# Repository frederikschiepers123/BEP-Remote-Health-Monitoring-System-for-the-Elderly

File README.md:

# Remote Health Monitoring System for the Elderly

TU Delft BSc Applied Project (BAP). A three-tier system that passively monitors
an elderly person at home — mmWave radar vitals (heart/breath rate, presence),
environment, air quality, light — and delivers the data to a hospital-side
FHIR R4 endpoint, with a smart-mirror UI in the home:

```
┌──────────────────┐   MQTT/mTLS   ┌──────────────────────┐   MQTT/mTLS   ┌──────────────┐   FHIR R4   ┌──────────┐
│  Sensor module   │ ────────────► │  Android tablet      │ ◄──────────── │  SBC         │ ──────────► │ Hospital │
│  Pico 2 W (C11)  │               │  Mosquitto broker    │               │  aggregator  │             │ endpoint │
│  radar/env/air/  │               │  + MagicMirror² UI   │               │  (Python,    │             │ (HAPI in │
│  light + OLED    │               │  behind the mirror   │               │  sbc/)       │             │  dev)    │
└──────────────────┘               └──────────────────────┘               └──────────────┘             └──────────┘
```

Every byte between tiers is mTLS-encrypted (ECDSA P-256, project CA, static
factory-provisioned certs). The firmware publishes raw JSON samples on
`rmms/<uuid>/...`; the mirror and the SBC are independent subscribers of the
same topics.

## Read this first (in order)

1. **[`CLAUDE.md`](CLAUDE.md)** — the firmware + system architecture contract.
   Single source of truth; everything else defers to it.
2. **[`docs/CLAUDE_tablet.md`](docs/CLAUDE_tablet.md)** — the tablet tier
   (broker, MagicMirror², mDNS, presence→screen coupling, autostart).
3. **[`sbc/CLAUDE.md`](sbc/CLAUDE.md)** — the SBC aggregator / FHIR tier.
4. **[`docs/handover.md`](docs/handover.md)** — what is hardware-proven vs
   built-only, known hardware/network gotchas, and CA/cert custody.

## Repository map

| Path | What it is |
|---|---|
| `CLAUDE.md`, `DEMO.md` | The architecture contract and the end-to-end demo runbook (see reading order above / quickstarts below). |
| `main/`, `components/` | **Pico 2 W firmware** (C11; pico-sdk + FreeRTOS + lwIP/mbedTLS + littlefs). One component per concern — layout in `CLAUDE.md §6`. |
| `test/host/` | Native unit tests (CMocka) for driver logic — `bash test/host/run.sh`. |
| `test/bringup/` | Standalone bring-up/diagnostic firmware images (blink → sensors → Wi-Fi → mTLS → full bench). `bringup_sensors` is the demo image. |
| `docs/` | System docs: bring-up procedure, MQTT topic contract, pin map, ADRs, provisioning, handover, technical audit of the previous group's code. |
| `scripts/` | Operational scripts: build, CA + device provisioning, tablet deploy/boot, demo startup, broker ACL test. Index: `scripts/README.md`. |
| `sbc/` | **SBC aggregator** — standalone Python project (own README, RUNBOOK, CLAUDE.md, tests). Never compiled into the firmware. |
| `MagicMirror/` | Vendored upstream MagicMirror² tree (see its README). Project work lives only in `modules/MMM-SensorUI/`, `modules/MMM-CustomMQTTBridge/`, `css/`, `config/` — the live `config.js` holds LAN specifics, is gitignored, and lives on the tablet; `config/config.custom.sample.js` is a UI-only starter. |
| `HealthMonitorWakeTest/` | **Android wake app** (Android Studio project): radar presence ↔ tablet screen on/off via the localhost MQTT listener (ADR-0004). See its README. |
| `apk/` | Prebuilt APK of the wake app. |
| `fully/` | Exported settings for the optional Fully Kiosk Browser (mirror kiosk mode). |
| `third_party/` | Git submodules: FreeRTOS-Kernel, littlefs. **pico-sdk is not vendored** — see the firmware quickstart. |
| `documents_and_diagrams/` | Thesis report, defense presentation, system diagrams. |
| `papers/` | Reference papers + the complete reference list. |
| `lasercutting_files/` | Enclosure/acrylic lasercutting files (DXF + Fusion 360). |
| `PCB/` | This group's KiCad PCB design files + bench measurements (buck converter scope shots). |
| `Readout Code HMMD-MR60BHA2 and BMP/` | Standalone sensor-readout experiments (radar filtering tests, BMP readout) used during bring-up — not part of the production firmware. |

**Local / generated directories (never in git):** `build*/` are CMake output
trees; `out/` is provisioning output created by `scripts/provision_ca.sh` —
it holds device/broker/mirror certificate bundles **including private keys**
and must never be committed (it is gitignored; see `docs/provisioning.md`).
On a fresh clone neither exists until you build/provision.

The **previous BAP group's material** (`bestanden_vorige_BAP/`) was removed
from the tree during handover cleanup — it is reference-only and available in
git history (any pre-July-2026 commit). Their registration protocol was
audited (`docs/technical-audit.md`) and deliberately replaced
(`CLAUDE.md §9.4`); their committed private keys are burned — never reuse
anything cryptographic from that tree.

## Quickstart per tier

### Firmware (Pico 2 W)

```bash
git clone --recurse-submodules <this-repo>            # brings FreeRTOS-Kernel + littlefs
git clone https://github.com/raspberrypi/pico-sdk.git ~/pico/pico-sdk
(cd ~/pico/pico-sdk && git submodule update --init)
export PICO_SDK_PATH=~/pico/pico-sdk

mkdir build && cd build
cmake -DPICO_BOARD=pico2_w -DCMAKE_BUILD_TYPE=Debug ..
cmake --build . -j$(nproc)
# → main/sensor_module.uf2 (production) + test/bringup/*.uf2 (bring-up images)
```

Flash: hold BOOTSEL while plugging in, copy the `.uf2` to the mounted drive
(details + SWD alternative: `CLAUDE.md §5`). Bring-up order with expected
results per step: `docs/bring_up.md`. Host tests: `bash test/host/run.sh`.

### Certificates + device provisioning

Identity is factory-provisioned: certs are generated **off-device** by the
project CA and written to the Pico's littlefs; there is no enrollment protocol
(`CLAUDE.md §9.4`). The full procedure — CA creation, broker/mirror/operator/
device bundles, `bringup_provision.uf2` + `scripts/provision_device.py` — is in
**[`docs/provisioning.md`](docs/provisioning.md)**. The CA private key is *not*
in this repo; custody is covered in `docs/handover.md`.

### Tablet (broker + mirror)

`scripts/deploy_home_kit.sh` provisions/deploys the whole tablet kit over ssh
(Termux); `scripts/tablet_boot.sh` + Termux:Boot make the tablet self-healing
across reboots. Tier spec: `docs/CLAUDE_tablet.md`.

### SBC aggregator (FHIR)

```bash
cd sbc && python3 -m venv .venv && .venv/bin/pip install -e .[dev]
.venv/bin/python -m pytest tests -q
```

Full install/run/prove-the-FHIR-output walkthrough: `sbc/RUNBOOK.md`.

### End-to-end demo

Full session procedure: **[`DEMO.md`](DEMO.md)**. In short:
`scripts/demo_start.sh <tablet-ip>` starts a demo session; a provisioned Pico
running `bringup_sensors.uf2` publishes live sensor data and the mirror renders
it. Networking caveats (use a phone hotspot, not eduroam; keep the tablet
awake) are in `docs/handover.md`.

## Where the contracts live

- MQTT topics + JSON payload schema: `CLAUDE.md §9`, `docs/mqtt_topics.md`.
- Sensor-JSON → FHIR mapping: `CLAUDE.md §9.6` (firmware side) and
  `sbc/docs/fhir-mapping.md` (generated LOINC/UCUM table).
- Mirror UI boundary (raw topics, JS-side thresholds, two-namespace design):
  `CLAUDE.md §9.5`/`§9.5.1` and the module READMEs under `MagicMirror/modules/`.
- Cross-tier loss-tolerance + idempotency: `docs/sbc-failover-and-idempotency.md`.

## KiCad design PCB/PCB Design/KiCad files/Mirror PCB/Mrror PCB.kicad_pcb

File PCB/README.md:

# PCB/

- `PCB Design/` — all KiCad files.
- `Buck_images/` — oscilloscope photos from testing the buck-converter
  circuit on the PCB (directory names give the load condition).

## Which files are authoritative

- **Generic (sensor-module) board:**
  `PCB Design/KiCad files/Generic PCB/Generic PCB/Generic PCB.kicad_pcb`
  (+ matching `.kicad_sch`/`.kicad_pro`). Note the doubled `Generic PCB/`
  nesting is a KiCad project-folder artifact — descend twice.
- **Mirror board:**
  `PCB Design/KiCad files/Mirror PCB/Mrror PCB.kicad_pcb`
  (+ matching `.kicad_sch`/`.kicad_pro`).

Caveats for the next group:

- The `Mrror` spelling is a typo, but it is **load-bearing**: KiCad project
  files cross-reference each other by name — do not rename.
- Some `Mrror PCB*` artifacts (silkscreen PDFs, `Mrror_PCB_routed_v1.kicad_pcb`)
  also sit inside the *Generic* board's folder; the Mirror board's canonical
  files are the ones under `Mirror PCB/`.
- KiCad autosave/backup droppings (`_restore_backup_*`, `*.lck`, `*.bak`,
  `*_chatgpt*.zip`) were deleted at handover and are now gitignored.
- Known board erratum: the I²C bus lacks pull-ups — fit 4.7 kΩ from GP8/GP9
  to 3V3 (see `docs/handover.md`).

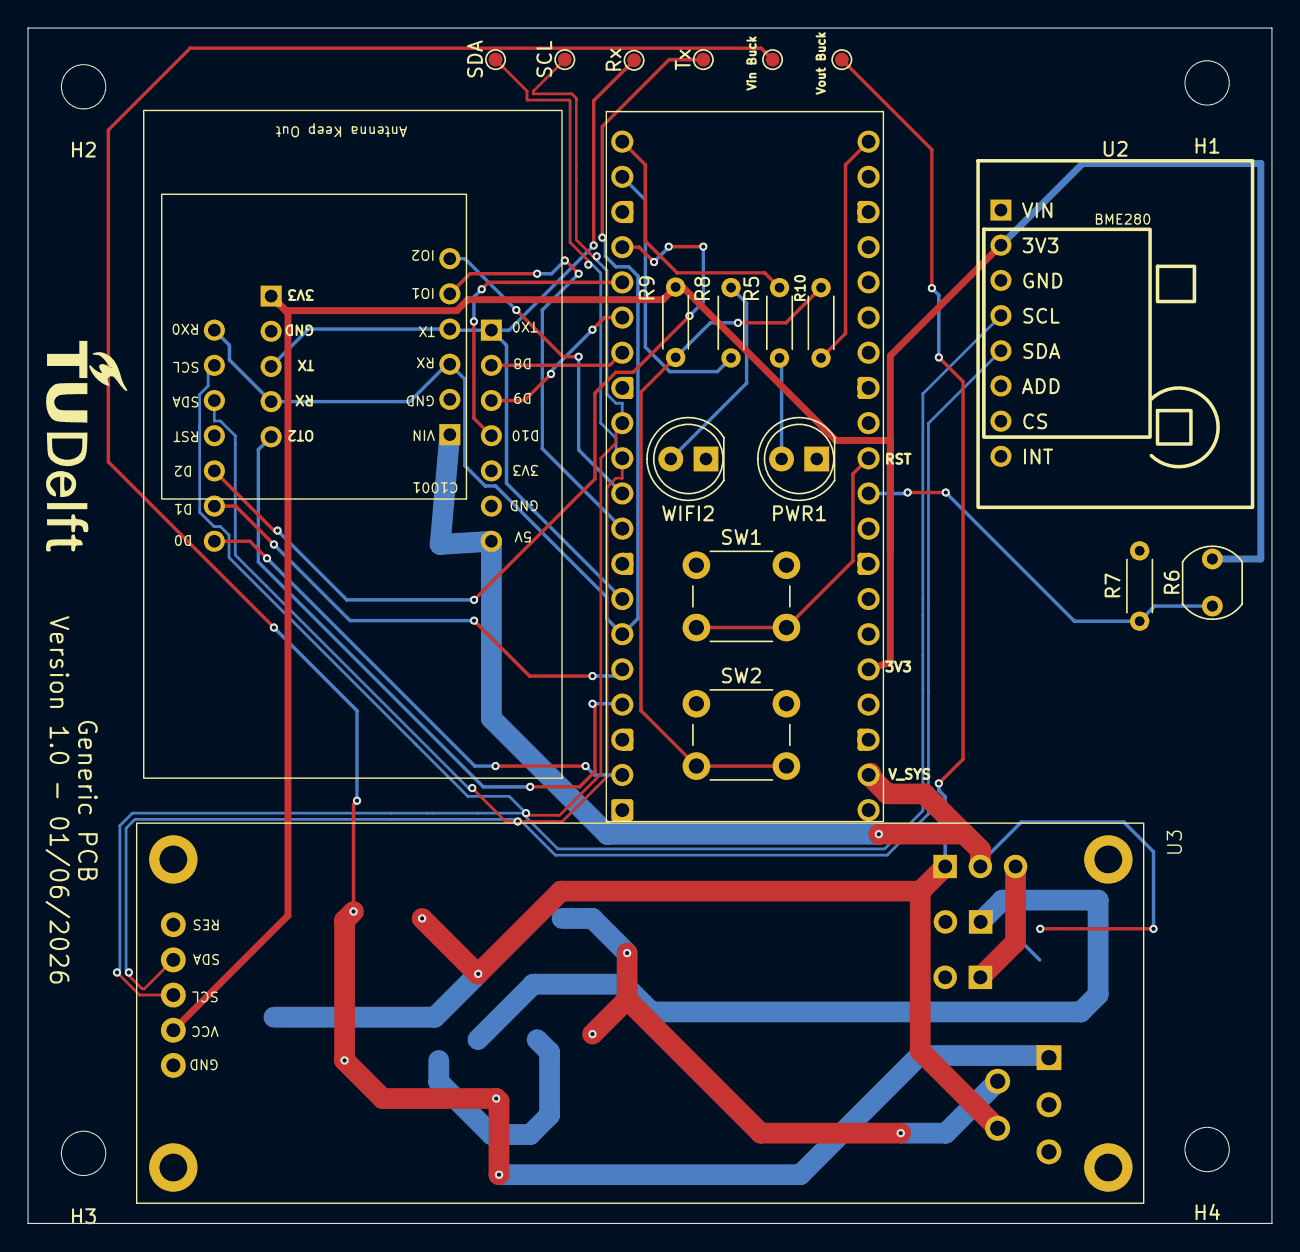
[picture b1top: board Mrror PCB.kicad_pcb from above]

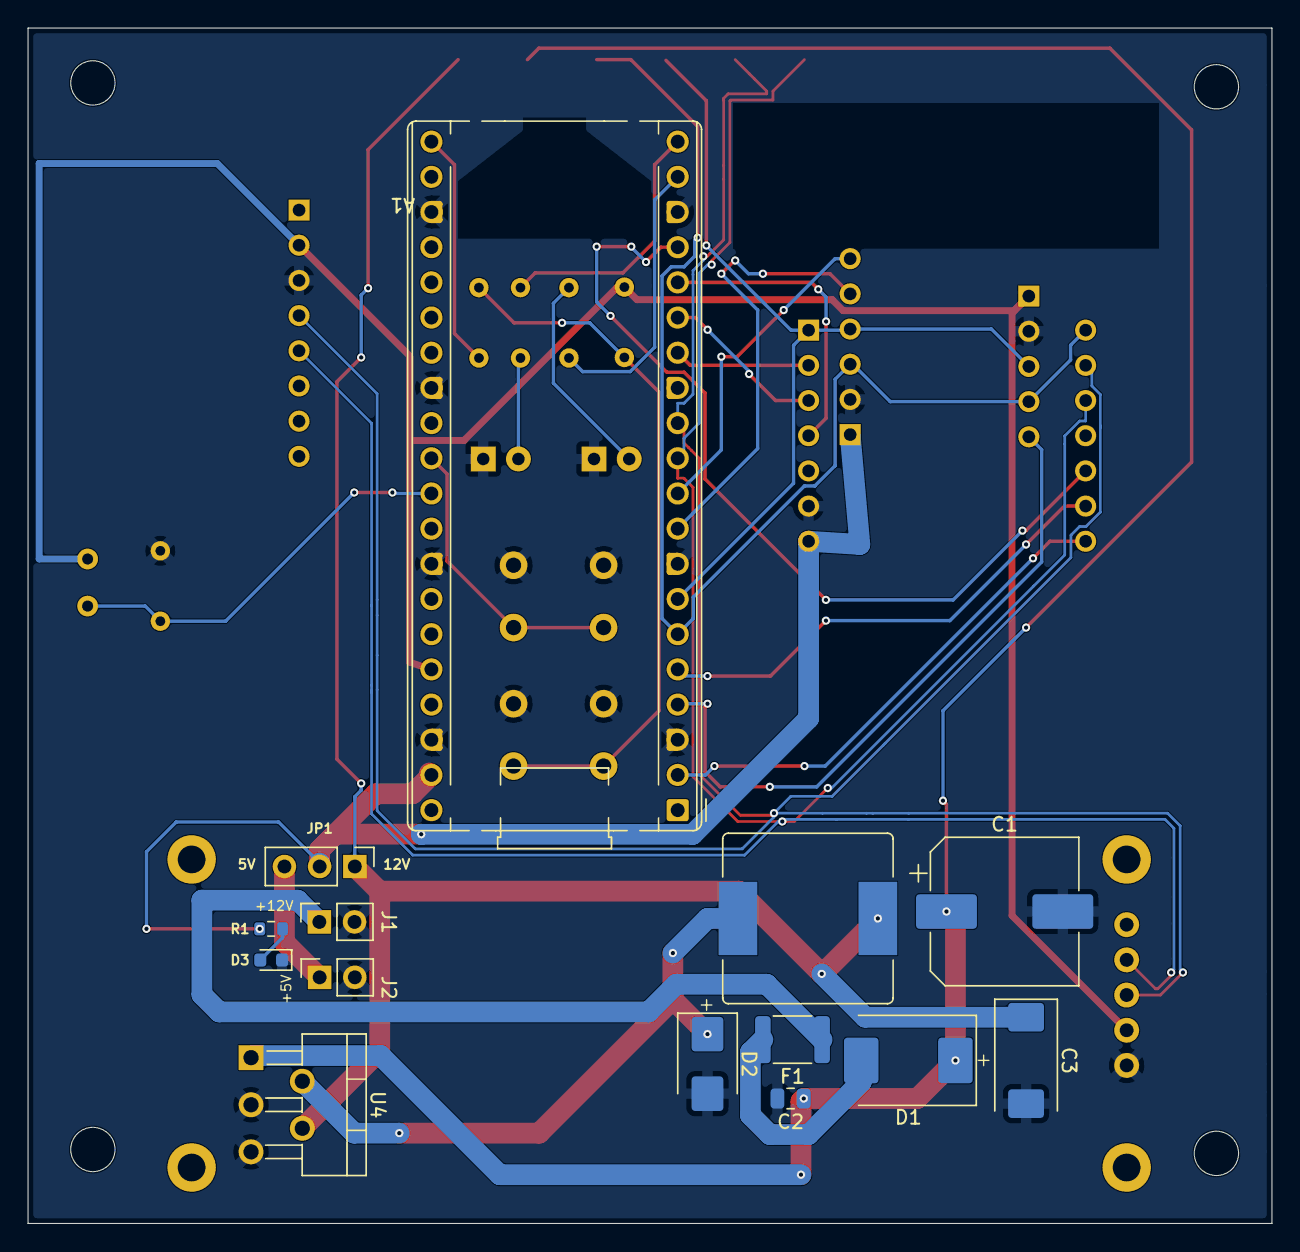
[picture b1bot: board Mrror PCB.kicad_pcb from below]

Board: 2 copper layers, 89.8 x 86.3 mm, 37 parts (14 on the bottom side), 31 nets.

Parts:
A1: RaspberryPi_Pico_W; RaspberryPi_Pico_Common_THT
C1: 680 uF; CP_Elec_10x10.5
C2: 100 nF; C_0805_2012Metric
C3: 330 uF; CP_EIA-7343-31_Kemet-D
D1: D_Schottky; D_SMC
D2: D_Schottky; D_SMB
D3: LED; LED_0603_1608Metric
F1: Polyfuse; Fuse_1812_4532Metric
H1, H2, H3, H4: MountingHole; MountingHole_3.2mm_M3
IC1: MR60BHA2
J1: 12V input; PinSocket_1x02_P2.54mm_Vertical
J2: +5V_IN; PinSocket_1x02_P2.54mm_Vertical
JP1: Jumper_3_Open; PinHeader_1x03_P2.54mm_Vertical
L1: 33 uH; L_Bourns_SRR1210A
PWR1: LED; LED_D5.0mm
R1: 1k; R_0603_1608Metric
R5, R8: 330; R_Axial_DIN0204_L3.6mm_D1.6mm_P5.08mm_Horizontal
R6: LDR07; R_LDR_5.1x4.3mm_P3.4mm_Vertical
R7, R9: 10k; R_Axial_DIN0204_L3.6mm_D1.6mm_P5.08mm_Horizontal
R10: 1k; R_Axial_DIN0204_L3.6mm_D1.6mm_P5.08mm_Horizontal
Rx: Rx; TestPoint_Pad_D1.0mm
SCL: SCL; TestPoint_Pad_D1.0mm
SDA: SDA; TestPoint_Pad_D1.0mm
SW1: Rst; SW_PUSH_6mm
SW2: Disp; SW_PUSH_6mm
Tx: Tx; TestPoint_Pad_D1.0mm
U2: ENS160 + AHT21; ENS160+AHT21
U3: OLED_2.08_256x64_I2C_SH1122; OLED Display
U4: LM2596T-5; TO-220-5_P3.4x3.7mm_StaggerOdd_Lead3.8mm_Vertical
Vin Buck: VIN_BUCK; TestPoint_Pad_D1.0mm
Vout Buck: +5V_BUCK; TestPoint_Pad_D1.0mm
WIFI2: LED; LED_D5.0mm

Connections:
+3V3: A1.36 (3V3), IC1.21 (3V3), R6.2, R9.1, U2.2 (3V3), U3.2 (VCC)
+5V_BUCK: C3.1, JP1.1 (A), L1.2, U4.4 (FB), Vout Buck.1 (1_1)
+5V_SYS: A1.39 (VSYS), IC1.7 (5V), IC1.15 (5V), JP1.2 (C), R1.2
/+5V_EXT: J2.1, JP1.3 (B)
/+12V_IN: F1.1, J1.1
/D0: A1.2 (GPIO1), IC1.14 (D0)
/D2: A1.17 (GPIO13), IC1.12 (D2)
/D8: A1.14 (GPIO10), IC1.2 (D8)
/D9: A1.15 (GPIO11), IC1.3 (D9)
/D10: A1.16 (GPIO12), IC1.4 (D10)
/FD: A1.10 (GPIO7), IC1.20 (FD)
/HP: A1.9 (GPIO6), IC1.19 (HP)
/OT2: A1.4 (GPIO2), IC1.25 (OT2)
/RGB: A1.5 (GPIO3), IC1.13 (D1_LED)
/SW: D2.1 (K), L1.1, U4.2 (OUT)
GND: A1.3 (GND), A1.8 (GND), A1.13 (GND), A1.18 (GND), A1.23 (GND), A1.28 (GND), A1.33 (AGND), A1.38 (GND), C1.2, C2.2, C3.2, D2.2 (A), D3.1 (K), IC1.6 (GND), IC1.16 (GND), IC1.22 (GND), J1.2, J2.2, PWR1.1, R7.2, SW1.1, SW2.1, U2.3 (GND), U3.1 (GND), U4.3 (GND), U4.5 (~ON/OFF), WIFI2.1
I2C0_SDA+: A1.11 (I2C0_SDA), IC1.10 (SDA), SDA.1 (1_1), U2.5 (SDA), U3.4 (SDA)
I2C0_SDA-: A1.12 (I2C0_SCL), IC1.9 (SCL), SCL.1 (1_1), U2.4 (SCL), U3.3 (SCL)
unnamed: A1.19 (GPIO14), R8.2
unnamed: A1.20 (GPIO15), R5.1
unnamed: A1.21 (GPIO16), R10.1
unnamed: A1.31 (GPIO26_ADC0), R6.1, R7.1
unnamed: A1.30 (RUN), SW1.2
unnamed: D1.2 (A), F1.2
unnamed: D3.2 (A), R1.1
unnamed: PWR1.2, R5.2
unnamed: R8.1, WIFI2.2
unnamed: R9.2, R10.2, SW2.2
Rx: A1.7 (GPIO5), IC1.1 (Tx0), IC1.18 (Tx0), IC1.23 (TX), Rx.1 (1_1)
Tx: A1.6 (GPIO4), IC1.8 (Rx0), IC1.17 (Rx0), IC1.24 (RX), Tx.1 (1_1)
VIN_BUCK: C1.1, C2.1, D1.1 (K), U4.1 (VIN), Vin Buck.1 (1_1)

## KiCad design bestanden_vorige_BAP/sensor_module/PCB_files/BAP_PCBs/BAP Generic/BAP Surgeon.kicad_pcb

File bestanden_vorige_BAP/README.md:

> **Previous BAP group's material — reference only.** This directory is an
> unmodified copy of the 2025 group's repository (their own README follows
> below; its folder names don't fully match — `sbc_software`/`sensor_module_software`
> are `SBC`/`sensor_module` here). Their MicroPython firmware is a behavioural
> spec, not a starting point, and their registration protocol was **audited and
> deliberately replaced** — see the repo-root `docs/technical-audit.md` and
> root `CLAUDE.md §1/§9.4` before reusing anything from here.
>
> The private keys the previous group committed (the audit's §D.1 finding)
> have been **deleted from this copy**; treat any key material that ever
> lived here as burned. Never reuse it.

# Registering Medical Devices - Registering Medical Devices
This is the README file for the registration protocol that is the result of the Bachelor's Graduation Project. 
The contents of this module implement a protocol that can register different kinds of peripheral devices for a RMMS. In this README the contents of every software file will be described, as well as the workflow to register devices.

### This folder contains the following:
- `./papers:` A folder containing all papers and cites used in this Bachelor Afstudeer Project.
- `./registration_software:` The registration software for camera's, sensor modules and SBC's.
- `./sbc_software:` The registration and connection software for the SBC's.
- `./sensor_module_software:` The registration, connection and sensor software for the sensor modules. Also incluces hardware design files.
- `./sensor_module:` The registration, connection and sensor software for the sensor modules. Also incluces hardware design files.
- `./mosquitto` and `./resources`: Configuration files and certificates used by the software. 

### Table of Contents  
- [Registering Medical Devices - Registering Medical Devices](#registering-medical-devices---registering-medical-devices)
    - [This folder contains the following:](#this-folder-contains-the-following)
    - [Table of Contents](#table-of-contents)
  - [Settings](#settings)
  - [Run the Registration Program](#run-the-registration-program)
    - [Prerequisites](#prerequisites)
  - [Label generator:](#label-generator)
    - [How it works:](#how-it-works)
    - [How to use:](#how-to-use)
  - [Active LED Identification](#active-led-identification)
    - [How it Works](#how-it-works-1)
    - [How to Use](#how-to-use-1)
    - [Camera Calibration](#camera-calibration)
  - [Sensor Module and SBC Registration:](#sensor-module-and-sbc-registration)
    - [How it Works](#how-it-works-2)
    - [How to use](#how-to-use-2)
  - [Camera registration:](#camera-registration)
    - [How it works:](#how-it-works-3)
    - [How to use:](#how-to-use-3)
      - [Camera Registration Settings](#camera-registration-settings)
  - [Sensor Module Tools](#sensor-module-tools)
    - [How it works:](#how-it-works-4)
    - [How to use:](#how-to-use-4)
      - [Flash + Restore](#flash--restore)
      - [Backup from device](#backup-from-device)
      - [Upload to device](#upload-to-device)

## Settings
All settings can be found in the file: `registration_software/common/config.py`. Settings are grouped using dataclasses to maximize readability. Settings are imported using: `from registration_software.common.config import settings`.

## Run the Registration Program
To run the registration program, the user can run the following command from an ubuntu terminal, which is working in the top level of this folder. This is the folder in which the `deploy.sh` is located:\
`sudo ./deploy.sh`\
After running this command, a virtual environment and mosquitto broker are set up and ready to use. Run `sudo ./registration.sh` from the same folder to actually run registration, then follow the prompts that are given by the scripts. When registration is finished, a clean table can be found in your browser, as mentioned by the prompts. The json file that contain the table can be found in `registration_software/resources/device_registry.json`

### Prerequisites
To ensure correct MQTT operation, a certificate authority should be provided. This can be done manually by placing a CA certificate and key in `registration_software/creds`. If no external CA certificate is required, a self-signed one can be created by choosing "A" after running the `./deploy.sh`. For now a certificate and key have been placed for every device, to make them ready to use. In the future these can be removed or overwritten if required. Make sure all devices have the same CA in their file tree.

## Label generator:
The Label generator can be found in: `registration_software/labels/label_generator.py`. It consist of a single Class called LabelGenerator(). 

### How it works:
The label generator generates unique labels. These labels will then be encoded into a QR code together with a signature
generated based an a private key and the label. These QR codes will then be saved as a .png file. The labels will also 
be saved separately to keep track of already existing labels.

### How to use:
In order to generate a number of labels first an instance of the class has to be created.
Afterwards `your_instance.generate(amount=, position=)` can be called.

Here `amount` is an integer that stands for the amount of labels/QR codes you want to create.

`position` is also an integer and determines the position of the label relative to the QR code.\
If not specified otherwise `position` is set to `1`. In this case the label will be placed directly above the QR code.\
If `position` is set to `2` the label will be placed to the right of the QR code.\
If `position` is set to `3` the label will be placed to the right of the QR code.

## Active LED Identification
The active LED identification used for registering sensor modules and SBS's is wrapped in a class `ActiveIdentificationTracker` in the file: `registration_software/identification/active_identification.py`. It combines video streaming, QR code detection, visualization and the LED identification algorithm to keep track devices in the camera FOV.

Note: active LED identification is already implemented for SBC and sensor module registration and does not need to be called separately.

### How it Works
The tracker is the device manager used to track and update devices in the FOV of the registration camera. It uses an output queue to communicate events with the registration software.

**The following components are used by the tracker:**
- `File/NetworkStreamer` found in `registration_software/interface/streamers.py`:\
    Either the file or network-streamer can be used to stream video from a source. Used as a live streamer for real-time data processing.

- `QrCodeDetector` found in `registration_software/identification/processing/qr_detector.py`:\
    The QR code detector used to detect, decode and verify QR codes in the video frame. Used as a seperate process to not interfere with the main thread. events are handled asynchronously.

- `LEDDetector` found in `registration_software/identification/processing/led_detector.py`:\
    The core of the LED identification algorithm. Used as part of the main thread every frame for real-time data processing.

- `Visualizer` found in `registration_software/interface/visualizer.py`:\
    The class handling the feedback window to give feedback to the user. Used as a seperate process to not interfere with the tracker. Is updated every frame for real-time data visualization.

- `DeviceState` found in `registration_software/models/device.py`:\
    A dataclass representing a device being tracked. Contains all data about the device necessary for the tracker.

### How to Use
The first step to use active identification is making sure the settings are set correctly in the config file under: `QrConfig`, `CameraConfig` and `ActiveIDConfig`. Make sure the QR code and active identification settings are set correctly. Change the camera settings to match the camera you are using. Use the camera calibration tool (Explained below) if you wish to use it.

To use the ActiveIdentificationTracker, it must first be initialized and started, then polled for events. The tracker should be initialized using the helper function `get_tracker()` from `registration_software/identification/__init__.py`. 
```
get_tracker(manual_source: str | int = None) -> ActiveIdentificationTracker:
    manual_source: (Optional) Overrides the camera source defined in the settings. It can be an integer (for a USB camera) or a string (for a file path or URL).
```

Since the tracker uses threading, it must be started to begin processing video frames using `tracker_object.start()`.

The tracker communicates results via a queue. Use the `get_events()` method to check for new updates. This returns `None` if the queue is empty or a dictionary containing the event type and device label. **Event Types:**
    
    IdentificationEvent.DEVICE_FOUND: A valid QR code has been detected and added to the tracking list.

    IdentificationEvent.IDENTIFIED: The LED blinking pattern of a device has been verified. The device status is updated to DeviceStatus.IDENTIFIED.

When the identification process is complete, call tracker_object.stop() to close the video stream and terminate the processing thread.

### Camera Calibration
The active identification estimates distance between the camera and the devices and uses it to give feedback to the user. This feedback is useful for correct camera and device placement. **The steps:**
1. Update the settings with the correct camera specifications. This includes:
    - IP Address. Set to None for auto discovery (time consuming).
    - Discovery Port (Default: 80 for http discovery on ONVIF cameras).
    - Username and Password.
    - Focal Length.
    - Sensor Width and Height.
2. Run the calibration tool using `run_camera_calibration_tool()` found in `registration_software/tools/calibrate.py` and follow the instructions.
3. Update the settings with distance constant, near limit and far limit given by the calibration tool.
4. The software now estimates the distance between the camera and devices and gives feedback to the user. The Visualizer will show if a device is too close or too far, as well as display the estimated distance.

Note: to disable the distance estimation, simply set the near and far limit to 0.0 and 'inf' respectively. The Visualizer will still show the distance estimation, but this can be ignored.

## Sensor Module and SBC Registration:
The algorithm for registering devices using MQTT can be found in `registration_software/registration/registration_client.py`. This makes use of a single class that first collects devices on the network, and then runs them all through the same cycle.

### How it Works
The `RegistrationClient` class runs through three phases. In the first phase it collects device that want to register by broadcasting periodic requests. In the next phase it checks authenticity of devices with a nonce challenge as well as finding out if their LED turns on in the correct moment. Based on these challenges it assigns labels and credentials. In the final phase it verifies if all devices are fully registered by sending checkups and requesting a final LED response. \

### How to use
To use the class it needs to be initialised. The three phase pipeline within the class is started automatically. During this initialisation a few variables need to be passed. \
**Variables:**
`CAManager: object`: handles anything related to certificates, meaning the generation and signing of them. Can be found in `registration_software/registration/ca_manager.py`.\
`DeviceRegistry: object`: handles the registry table file, can append to that and make sure there are no double entries. Can be found in `registration_software/common/registry`. \
`ActiveIdentifationTracker: object`: tracks LEDs that blink during registration. This is the class that has been explained earlier.\
`manual: bool`: gives the user the ability to manually fill in labels. \
`auto: bool`: determines if the script waits for a final user input in the third phase or just continues. \

## Camera registration:
The camera registration algortihm can be found in 
`registration_software/identification/passive_identification.py`, it consist of a single Class called `Cam_register()`. 

### How it works:
The `Cam_register()` function compares the translations from all secondary camera to a to the main camera and vice versa. By matching translations it assigns the correct label to the correct camera, UUID, etc. 

### How to use:
Before starting the registration algorithm the setup is important. Place all the camera's on a straight line across from one camera. This camera will be used as the main camera, all other cameras will be called secondary cameras. Make sure all the secondary cameras are facing the main camera and that main camera is facing the secondary cameras. Make sure all the cameras are turned on, connected to the same wifi network and that they have the same onvif credentials. Next, fill in the settings in the config file. All the settings that are of importance for `Cam_register()` can be found in the config file: `registration_software/common/config.py`

#### Camera Registration Settings
The meaning of each variable is also explained here. 

After specifying the variables and settings needed for your use case. In order to use the Cam_register you have to create an instance of the class and call `your_instance.start()`.\
When runnin the deploy script this will be done automatically.\
However there are a couple of variables that can be passed when creating the instance of your class. For most use cases these variables can be left untouched. If the setup and setting in the config file are correct the algorithm should be ready for use.\

But if you do want to change these variables it can be done in
BAP-protocol/registration_software/\_\_init__.py under:\
    `det = Cam_register("set variables here")`

**These variables include:**\
`Cam_register(`
- `one_cam=`
- `change_password=`
- `password=`
- `save_results=`

`)`\
All variables are set to `False` if not specified otherwise, except for `password` which is set to `None` unless 
specified otherwise. \
\
`one_cam`: Normally the algorithm will assume there should be more than 1 camera in the FOV of the main camera. 
So if you want to use this algorithm when only using 1 secondary camera (so 2 cameras in total), `one_cam=` must be set to `True`.\
\
`change_password` is used to change the ONVIF device credential of the succesfully registered cameras. 
Because changing the ONVIF credentials of a device using python is not always succesfull/allowed depending on the manufacturer.
This variable is normally set to `False`. \
The algorithm is designed to generate a random password, if you prefer to use
your own password this can be done by passing it as a string to the variable `password`.\
Since not all devices support/allow changing device credentials using python, it is important to be cautious when setting 
this variable to `True`. 

`save_results` can be set to `True` if you want to save the QR code scanning results. This includes the frame recieved 
from the camera as well as the ouput of the QR code detector for that frame.\
`save_results` is mainly intended give insight into the output of the cameras. This may be usefull whan a specific 
camera does not seem to produce any results. The results are saved to a file named after the IP address of each camera.

## Sensor Module Tools
The sensor module tools can be found at: `Sensor_module/tools/dist/ucontroller_tools.exe`.\
This exe file includes tools for flashing the device, uploading files to the device and backing up the device.

>[!warning]
>The backup tools only work when the .exe file has the correct permissions, thus check the folder you want to upload your backup to and/or give the executable permission for controlled folder access.

### How it works:
The sensor module tool makes use of mpremote to access the REPL of the microcontroller from the computer in order to manage the files on the microcontroller and upload files from the computer or download files from the microcontroller. \
For flashing it uses the esptool to flash the microcontroller firmware to the memory of the microcontroller. This flashing is done by using binary(.bin) files.

### How to use:
Launch the exe file by double clicking the it. When it has started there will be three tabs with three different functionalities: flash + restore, backup from device, upload to device.

#### Flash + Restore
In order to flash a microcontroller you first want to put it in boot mode.\
The microcontroller is put into boot mode with the following steps:\
1. hold the boot button(The left button on the front of the Lilygo TQ-T Pro)
2. press the reset button(little black button on the left side of the microcontroller)
3. release the boot button.
Now you can press the button `Refresh ports` to refresh all the input ports, and select the correct `Flash Port` from its dropdown menu.\
Select the correct binary(.bin) at `Firmware .bin` the file is found in `Sensor_module/bin_files/T-QT-Pro-firmware_4mb.bin` 

>[!Note]
>This binary file is specifically for the Lilygo TQ-T Pro with 4mb of memory and 2mb of PSRAM.

Select the correct `Restore folder` next the folder is `Sensor_module/microcontroller_files/` in our project files.\
The next section presents different settings for flashing the microcontroller: 
 - `Flash firmware` enables the flashing of the firmware specified atif not it just uploads the files. 
 - `Erase flash before writing` enables the abbility to erase the previous flash before writing the new firmware to the microcontroller.
 - `Restore files after flash` enables the writing of the files within the selected `Restore folder`.
 - `Reset after restore` enables you to reset the microcontroller at the end of the process.
the standard baud rate is 460800 Hz and the standard waiting time for the REPL port is 30 seconds.

Click the button `Run Flash + Restore` to let the program run.\
the previous firmware will be removed and the new firmware will be uploaded.\
Halfway through running the program the flash will be completed and the executable will look for the REPL port of the microcontroller.\
The microcontroller needs to be reset in order to exit boot mode and then the REPL port will be detected automatically.\
All the files within the `Restore folder` are uploaded.\
The microcontroller resets itself when the upload is finished.

#### Backup from device 
Select the correct `REPL port` this is the COM port the microcontroller is connected to.\
choose the `Base folder` for the device backup.\
Click `Run Backup` to backup all the files from the microcontroller.

#### Upload to device 
Select the correct `REPL port` this is the COM port the microcontroller is connected to.\
Select if you want to upload a single file or directory.\
Select the corresponding path for the directory or file.\
Input the destination for the directory or file at `Remote path (folder or file)`.\
Select the options you want:
 - `Clear destination folder first (folder upload only)` removes the destination first and creates a new folder with all the selected directory you want to upload. tThis works only if you want to upload a whole directory.
 - `Reset after upload` resets the microcontroller after the files have been uploaded.

Click `Upload to device` to upload the selected file(s) to the microcontroller.

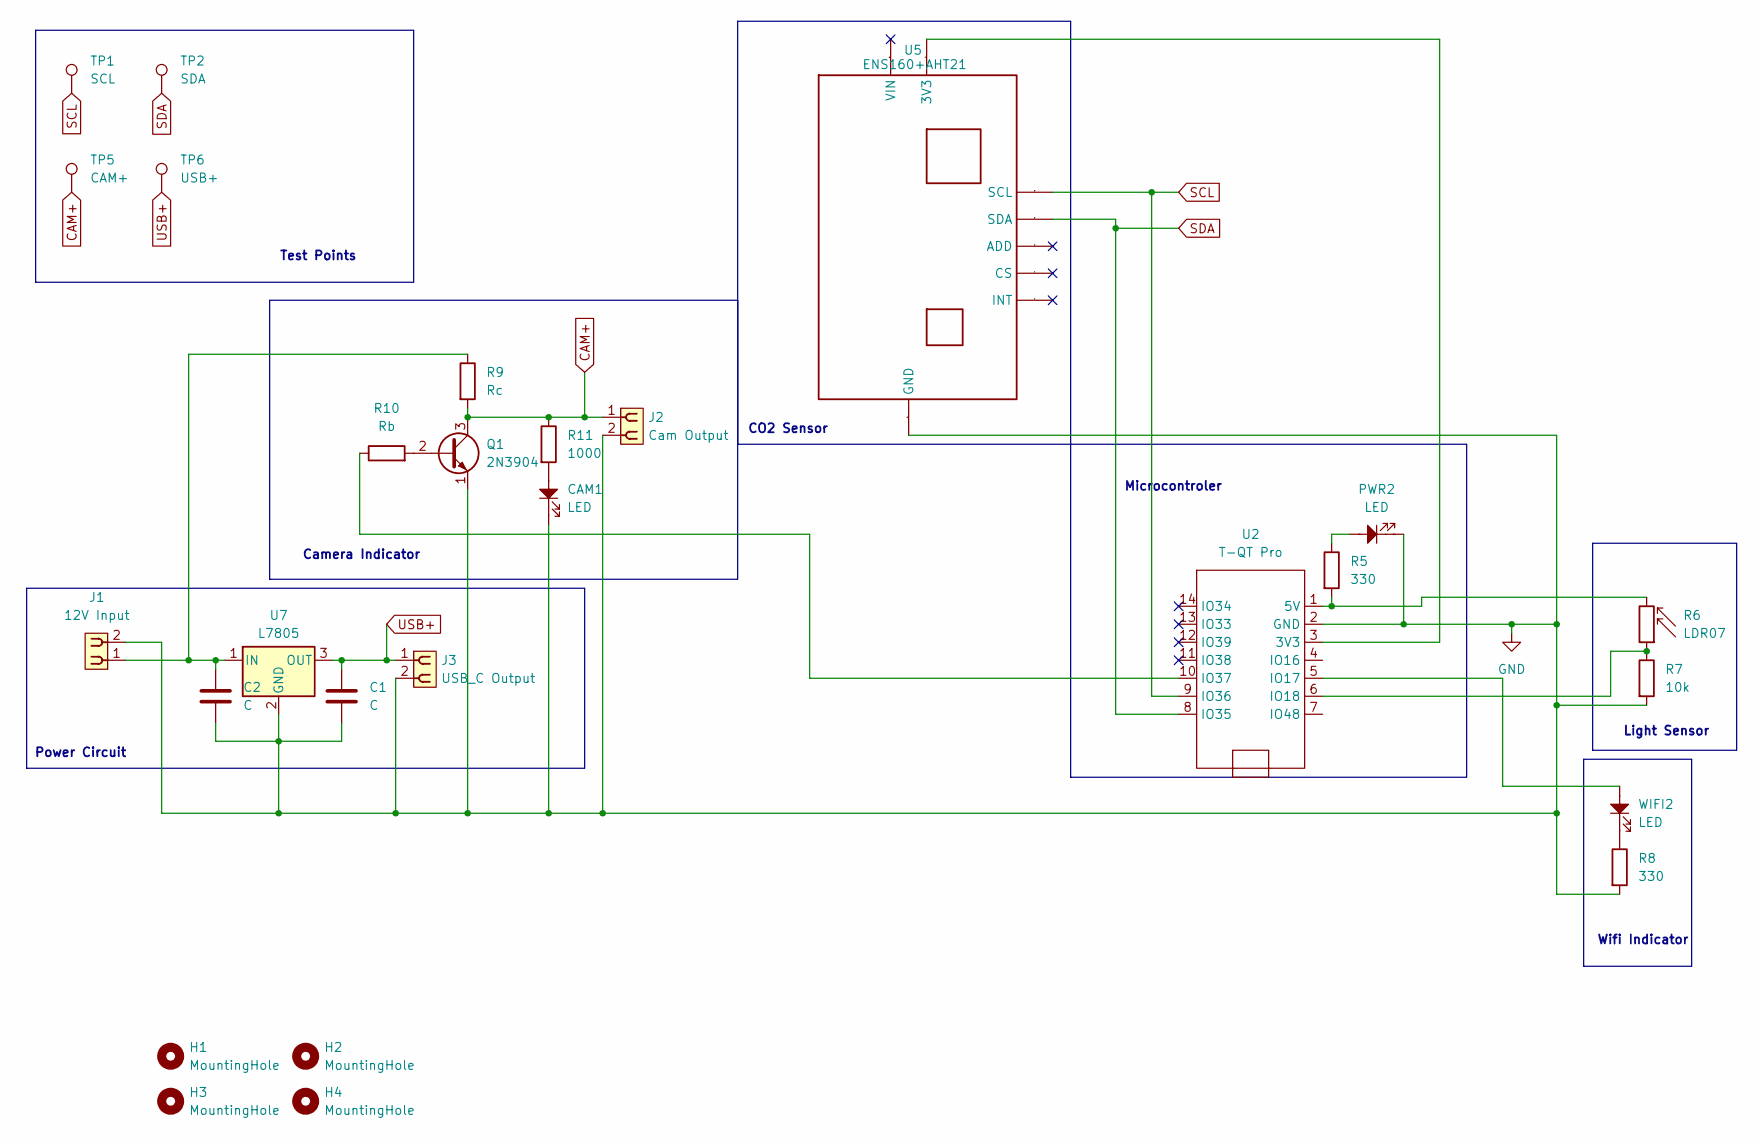
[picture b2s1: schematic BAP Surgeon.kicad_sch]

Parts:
C1, C2: C; C_Disc_D3.0mm_W1.6mm_P2.50mm
CAM1: LED; LED_D5.0mm
H1, H2, H3, H4: MountingHole; MountingHole_3.2mm_M3
J1: 12V Input; PinSocket_1x02_P2.54mm_Vertical
J2: Cam Output; PinSocket_1x02_P2.54mm_Vertical
J3: USB_C Output; PinSocket_1x02_P2.54mm_Vertical
PWR2: LED; LED_D5.0mm
Q1: 2N3904; TO-92_Inline_Wide
R5, R8: 330; R_Axial_DIN0204_L3.6mm_D1.6mm_P5.08mm_Horizontal
R6: LDR07; R_LDR_5.1x4.3mm_P3.4mm_Vertical
R7: 10k; R_Axial_DIN0204_L3.6mm_D1.6mm_P5.08mm_Horizontal
R9: Rc; R_Axial_DIN0204_L3.6mm_D1.6mm_P5.08mm_Horizontal
R10: Rb; R_Axial_DIN0204_L3.6mm_D1.6mm_P5.08mm_Horizontal
R11: 1000; R_Axial_DIN0204_L3.6mm_D1.6mm_P5.08mm_Horizontal
TP1: SCL; TestPoint_Pad_D1.0mm
TP2: SDA; TestPoint_Pad_D1.0mm
TP5: CAM+; TestPoint_Pad_D1.0mm
TP6: USB+; TestPoint_Pad_D1.0mm
U2: T-QT Pro; LilyGO TQ-T Pro
U5: ENS160+AHT21; Manufacturer Part ENS160-AHT21 Air sensor
U7: L7805; TO-220-3_Horizontal_TabDown
WIFI2: LED; LED_D5.0mm

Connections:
CAM+: J2.1, Q1.3 (C), R9.2, R11.1, TP5.1
GND: C1.2, C2.2, CAM1.1, J1.2, J2.2, J3.2, PWR2.1, Q1.1 (E), R7.2, R8.2, U2.2 (GND), U5.3 (GND), U7.2 (GND)
unnamed: CAM1.2, R11.2
unnamed: PWR2.2, R5.1
unnamed: Q1.2 (B), R10.2
unnamed: R8.1, WIFI2.1
unnamed: U2.3 (3V3), U5.2 (3V3)
unnamed: R5.2, R6.2, U2.1 (5V)
unnamed: U2.5 (IO17), WIFI2.2
unnamed: R6.1, R7.1, U2.6 (IO18)
unnamed: R10.1, U2.10 (IO37)
unnamed: C2.1, J1.1, R9.1, U7.1 (IN)
SCL: TP1.1, U2.9 (IO36), U5.4 (SCL)
SDA: TP2.1, U2.8 (IO35), U5.5 (SDA)
USB+: C1.1, J3.1, TP6.1, U7.3 (OUT)

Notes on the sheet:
Test Points
CO2 Sensor
Camera Indicator
Microcontroler
Light Sensor
Power Circuit
Wifi Indicator

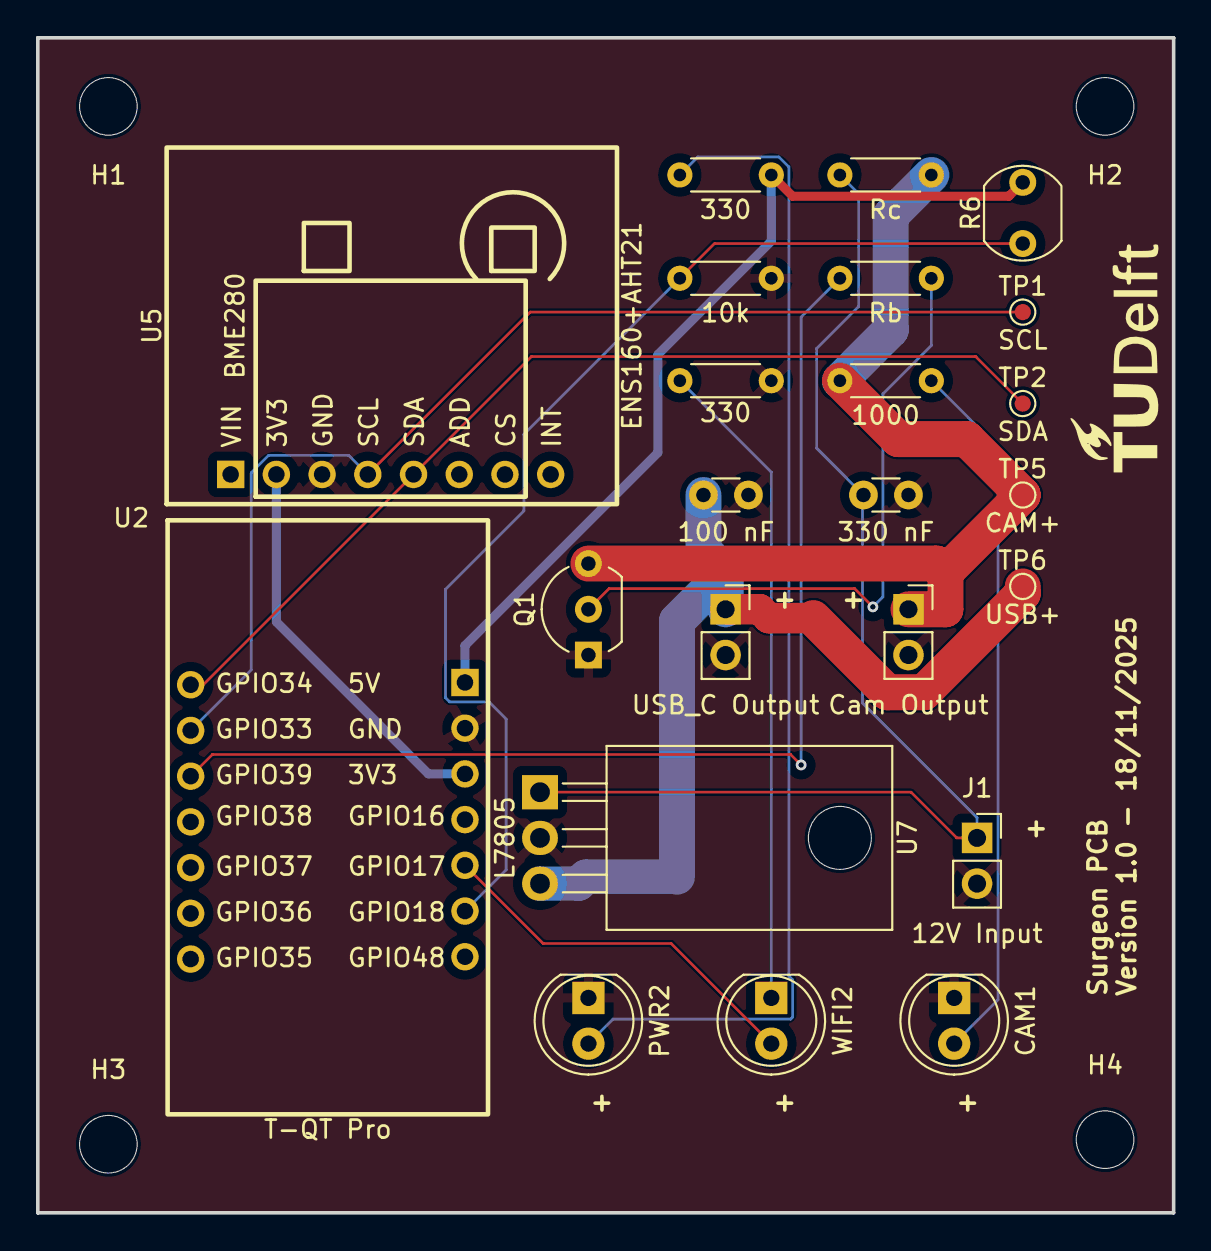
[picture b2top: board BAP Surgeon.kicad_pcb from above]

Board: 2 copper layers, 63.1 x 65.3 mm, 27 parts (0 on the bottom side), 15 nets.

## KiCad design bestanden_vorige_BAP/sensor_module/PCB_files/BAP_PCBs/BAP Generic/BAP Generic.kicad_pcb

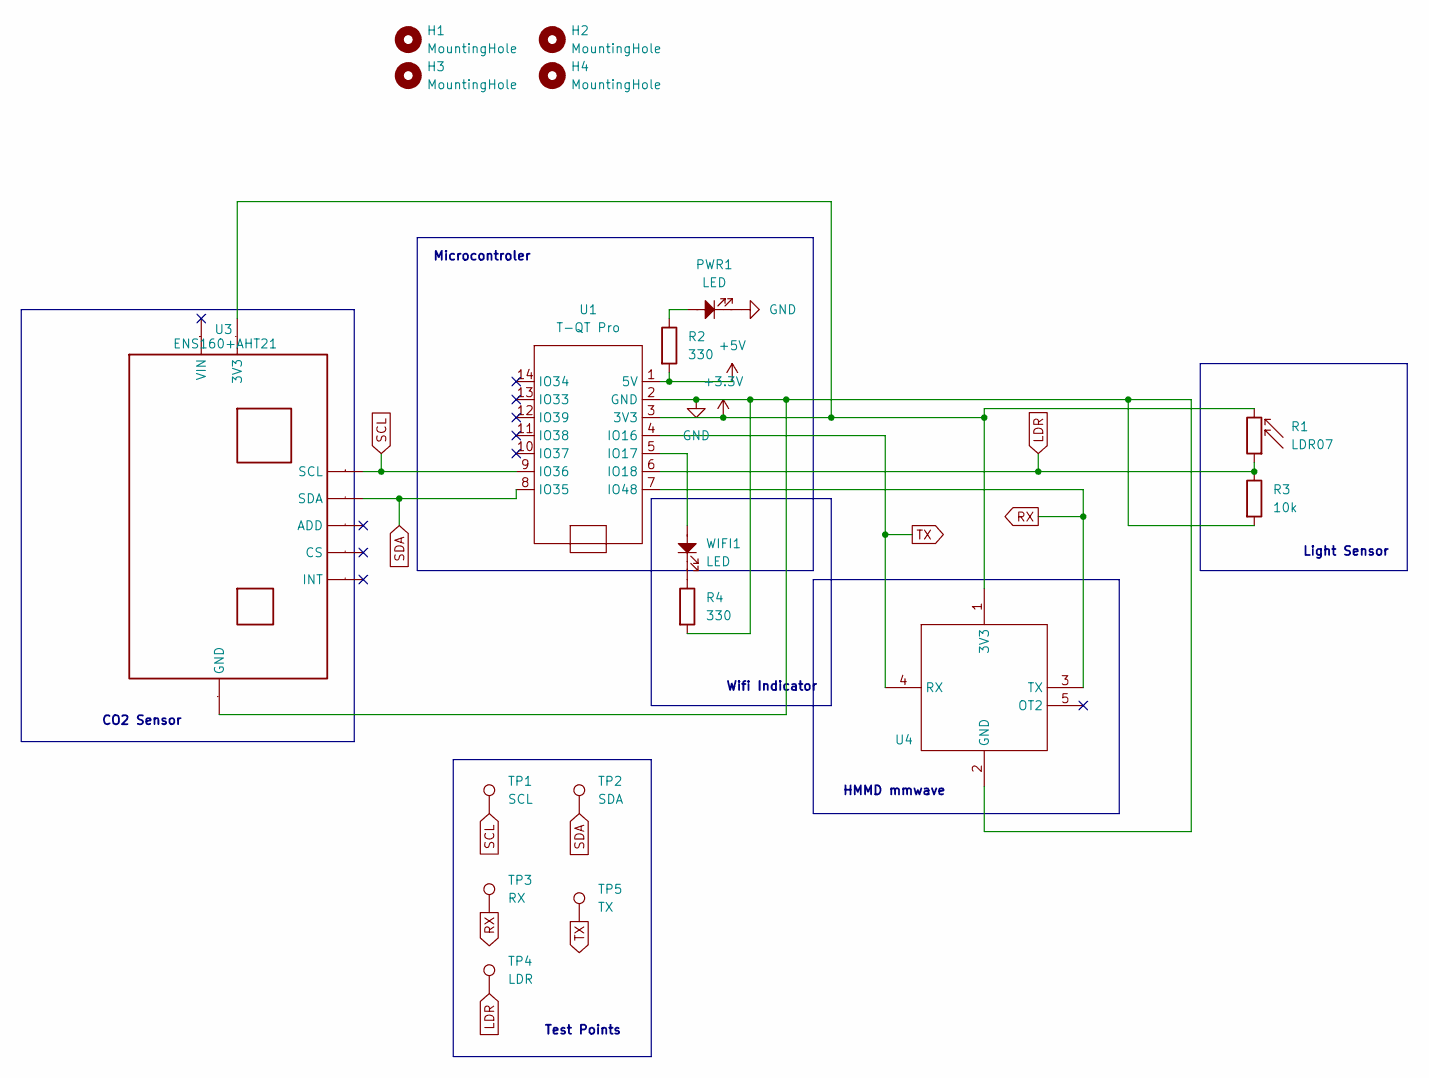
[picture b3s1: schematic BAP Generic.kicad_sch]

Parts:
H1, H2, H3, H4: MountingHole; MountingHole_3.2mm_M3
PWR1: LED; LED_D5.0mm
R1: LDR07; R_LDR_5.1x4.3mm_P3.4mm_Vertical
R2, R4: 330; R_Axial_DIN0204_L3.6mm_D1.6mm_P5.08mm_Horizontal
R3: 10k; R_Axial_DIN0204_L3.6mm_D1.6mm_P5.08mm_Horizontal
TP1: SCL; TestPoint_Pad_D1.0mm
TP2: SDA; TestPoint_Pad_D1.0mm
TP3: RX; TestPoint_Pad_D1.0mm
TP4: LDR; TestPoint_Pad_D1.0mm
TP5: TX; TestPoint_Pad_D1.0mm
U1: T-QT Pro; LilyGO TQ-T Pro
U3: ENS160+AHT21; Manufacturer Part ENS160-AHT21 Air sensor
U4: Foot_Mmwave
WIFI1: LED; LED_D5.0mm

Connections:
+3.3V: R1.2, U1.3 (3V3), U3.2 (3V3), U4.1 (3V3)
+5V: R2.2, U1.1 (5V)
GND: PWR1.1, R3.2, R4.2, U1.2 (GND), U3.3 (GND), U4.2 (GND)
LDR: R1.1, R3.1, TP4.1, U1.6 (IO18)
unnamed: PWR1.2, R2.1
unnamed: R4.1, WIFI1.1
unnamed: U1.5 (IO17), WIFI1.2
RX: TP3.1, U1.7 (IO48), U4.3 (TX)
SCL: TP1.1, U1.9 (IO36), U3.4 (SCL)
SDA: TP2.1, U1.8 (IO35), U3.5 (SDA)
TX: TP5.1, U1.4 (IO16), U4.4 (RX)

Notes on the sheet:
CO2 Sensor
Test Points
Microcontroler
HMMD mmwave
Light Sensor
Wifi Indicator

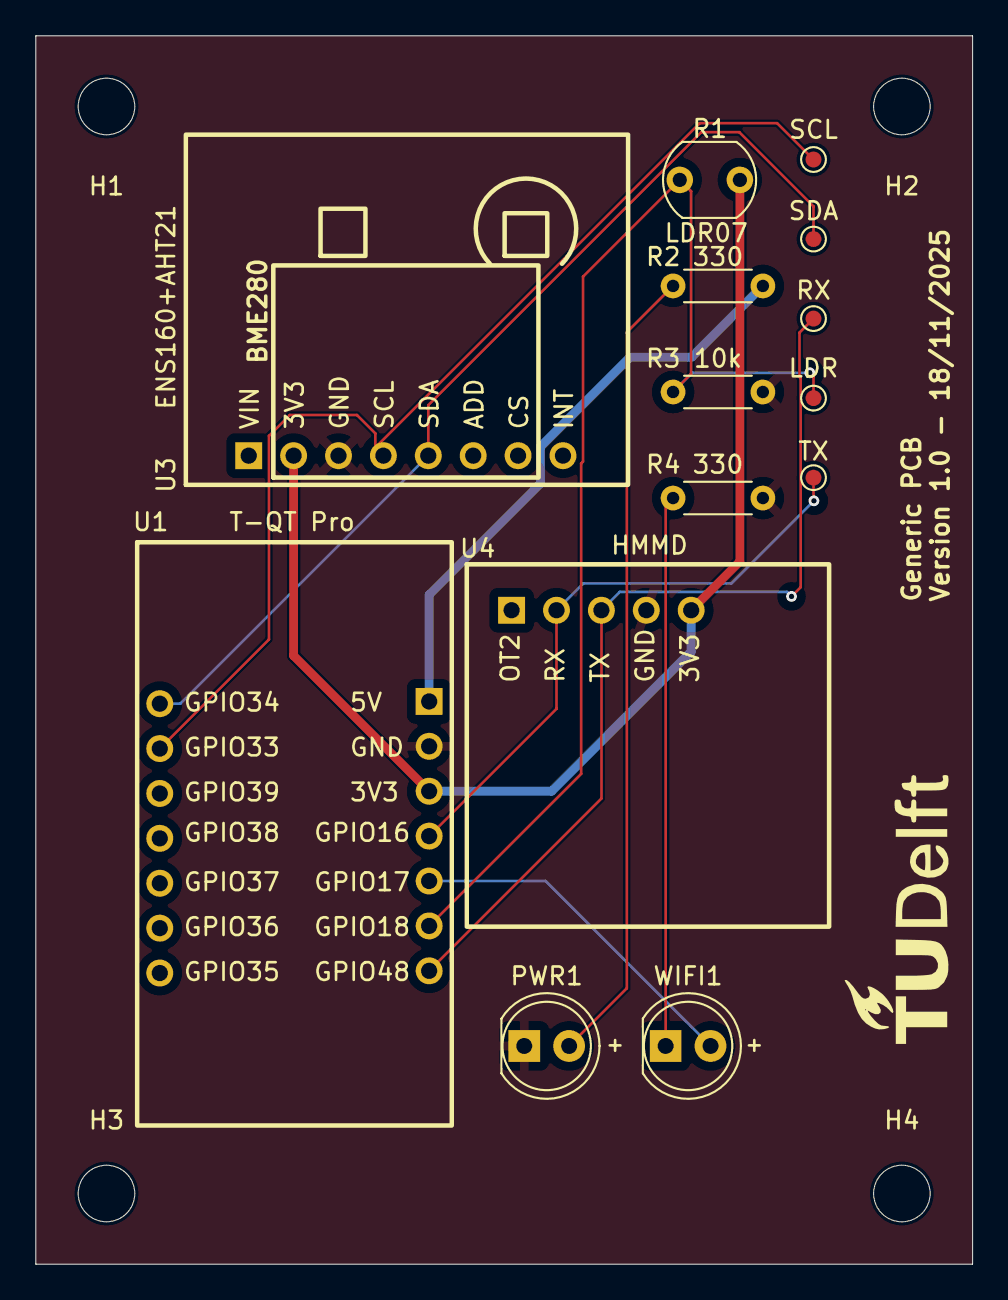
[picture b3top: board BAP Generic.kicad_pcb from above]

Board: 2 copper layers, 53.0 x 69.5 mm, 18 parts (0 on the bottom side), 11 nets.

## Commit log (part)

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2026-04-20 Initial project structure
2026-04-23 toevoegen folder met bestanden oude bap
2026-05-18 Added initial smart mirror (default/template)
2026-05-18 Revert "Added initial smart mirror (default/template)"
    This reverts commit eb0d1962b73c1ac72c6d9f8835fc65cb30df4c95.
    undo addition of smart mirror#
2026-05-18 Flatten MagicMirror into main repository
2026-05-18 Track MagicMirror modules after updating gitignore
2026-05-18 Flatten MagicMirror into single repository structure
2026-05-18 Testing if repository structure is now okay in vscode
2026-05-19 initial sensor design
2026-05-19 changed font, added al icons
2026-05-28 rudimentary version of screen with MQTT link
2026-05-28 changed layout, based on Canva sketch
2026-05-28 improved layout
2026-06-01 Make display relative to screen size
2026-06-02 updated ui
2026-06-05 mirror: bind 0.0.0.0 + open ipWhitelist so tablet browser can load MM²
2026-06-05 Add Android Studio project for elderly monitoring system
2026-06-05 Added vidconf
2026-06-05 Add HealthMonitorWakeTest Android application
2026-06-08 Add MMM-pages module
2026-06-08 icon color change on value, option to remove icons and color value instead
2026-06-08 Replace HealthMonitorWakeTest with updated version
2026-06-08 remove unneccesary files
2026-06-08 start app on boot
2026-06-10 Update MMM-SensorUI.js
    change display mode from "icons" to "colors"
2026-06-15 testing deployment of MM2 and android app
2026-06-15 Update deploy.sh
    added pkg upgrade -y
